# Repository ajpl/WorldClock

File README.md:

# WorldClock

This is a WorldClock implementation using Atmega 328 and DS1307 as a RTC.

## Inspiration

This project was inspired by [this](https://www.instructables.com/id/The-Wordclock-Grew-Up/) instructable that relies on a DS1302 instead of a DS1307. A couple of changes had to be made since these clocks work in different ways ([DS1302 Datasheet](https://datasheets.maximintegrated.com/en/ds/DS1302.pdf) and [DS1307 Datasheet](https://datasheets.maximintegrated.com/en/ds/DS1307.pdf)).

## How To
- Get all the parts necessary according to the Bill of Materials in Part 8 of the instructable linked above (for electronics you may use the schematic if you prefer)
- Etch the PCB using your favorite method or using a service like [OSH Park](https://oshpark.com)

- Flash the program into your Atmega 328 using your programmer of choice

- Solder every component into your PCB

- Test it out

- Follow the instructions linked above in order to build the clock's enclosure

- Put everything together

- Enjoy!

## Dependencies

- [RTC Lib](https://github.com/adafruit/RTClib)

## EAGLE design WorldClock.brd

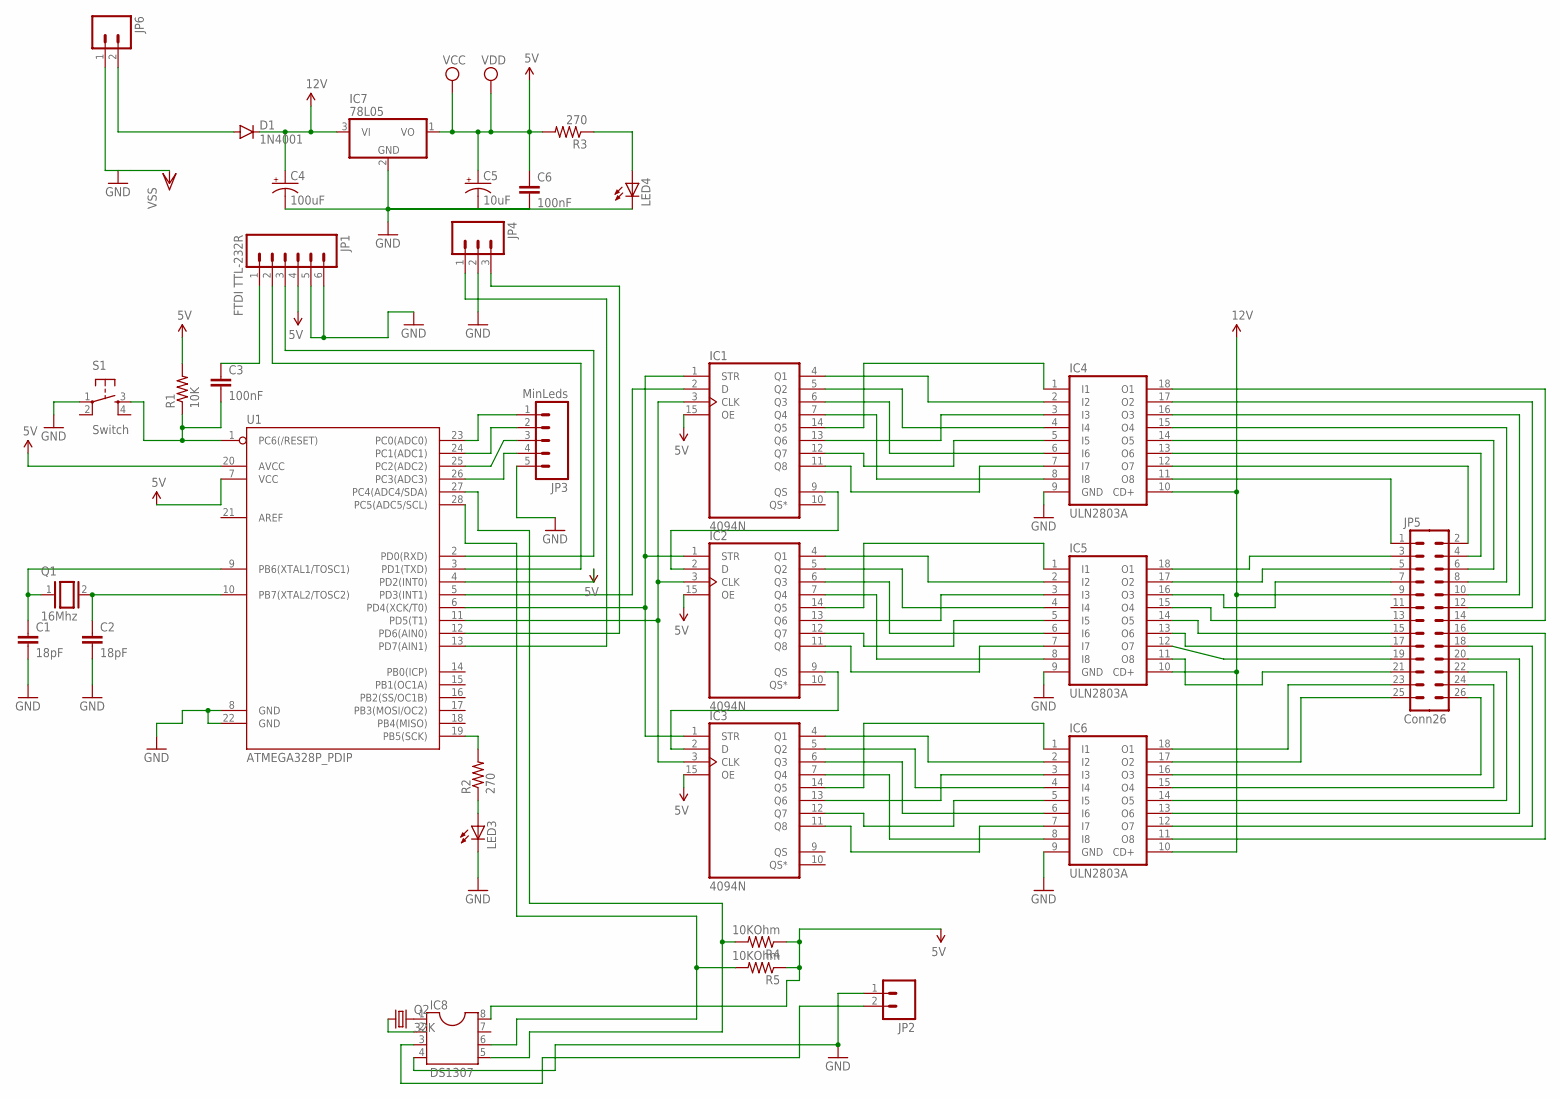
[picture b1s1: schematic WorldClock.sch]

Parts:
C1, C2: 18pF; CAP-PTH-SMALL2
C3, C6: 100nF; CAP-PTH-SMALL2
C4: 100uF; CPOL-RADIAL-100UF-25V
C5: 10uF; CPOL-RADIAL-10UF-25V
D1: 1N4001; DIODE-1N4148
IC1, IC2, IC3: 4094N; DIL16
IC4, IC5, IC6: ULN2803A; DIL18
IC7: 78L05; TO92
IC8: DS1307; SOCKET-08
JP1: FTDI TTL-232R; 1X06_NO_SILK
JP2, JP6: M025MM; SCREWTERMINAL-5MM-2
JP3: MinLeds; 1X05
JP4: M03-SCREW-5MM; SCREWTERMINAL-5MM-3
JP5: Conn26; 2X13
LED3, LED4: LED5MM
Q1: 16Mhz; QS
Q2: 32K; TC26V
R1: 10K; AXIAL-0.4
R2, R3: 270; AXIAL-0.4
R4, R5: 10KOhm; AXIAL-0.4
S1: Switch; TACTILE-PTH
U1: ATMEGA328P_PDIP; DIL28-3

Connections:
5V: C5.1 (+), C6.1, IC1.15 (OE), IC1.16 (VDD), IC2.15 (OE), IC2.16 (VDD), IC3.15 (OE), IC3.16 (VDD), IC7.1 (VO), IC8.8, JP1.4, R1.P$2 (2), R3.P$2 (2), R4.P$1 (1), R5.P$1 (1), U1.4 (PD2(INT0)), U1.7 (VCC), U1.20 (AVCC)
12V: C4.1 (+), D1.C, IC4.10 (CD+), IC5.10 (CD+), IC6.10 (CD+), IC7.3 (VI), JP5.9
GND: C1.2, C2.2, C4.2 (-), C5.2 (-), C6.2, IC1.8 (VSS), IC2.8 (VSS), IC3.8 (VSS), IC4.9 (GND), IC5.9 (GND), IC6.9 (GND), IC7.2 (GND), IC8.4, JP1.5, JP1.6, JP2.1, JP3.5, JP4.2, JP6.1, LED3.K (C), LED4.K (C), S1.1, U1.8 (GND), U1.22 (GND)
unnamed: C1.1, Q1.1, U1.9 (PB6(XTAL1/TOSC1))
unnamed: C2.1, Q1.2, U1.10 (PB7(XTAL2/TOSC2))
unnamed: C3.2, R1.P$1 (1), S1.3, U1.1 (PC6(/RESET))
unnamed: C3.1, JP1.1
unnamed: JP4.1, U1.13 (PD7(AIN1))
unnamed: JP1.2, U1.3 (PD1(TXD))
unnamed: JP1.3, U1.2 (PD0(RXD))
unnamed: JP4.3, U1.12 (PD6(AIN0))
unnamed: JP3.1, U1.23 (PC0(ADC0))
unnamed: JP3.2, U1.24 (PC1(ADC1))
unnamed: JP3.3, U1.25 (PC2(ADC2))
unnamed: JP3.4, U1.26 (PC3(ADC3))
unnamed: R2.P$2 (2), U1.19 (PB5(SCK))
unnamed: LED3.A, R2.P$1 (1)
unnamed: IC1.4 (Q1), IC4.2 (I2)
unnamed: IC1.5 (Q2), IC4.4 (I4)
unnamed: IC1.6 (Q3), IC4.6 (I6)
unnamed: IC1.7 (Q4), IC4.8 (I8)
unnamed: IC1.14 (Q5), IC4.1 (I1)
unnamed: IC1.13 (Q6), IC4.3 (I3)
unnamed: IC1.12 (Q7), IC4.5 (I5)
unnamed: IC1.11 (Q8), IC4.7 (I7)
unnamed: IC1.9 (QS), IC2.2 (D)
unnamed: IC2.4 (Q1), IC5.2 (I2)
unnamed: IC2.5 (Q2), IC5.4 (I4)
unnamed: IC2.6 (Q3), IC5.6 (I6)
unnamed: IC2.7 (Q4), IC5.8 (I8)
unnamed: IC2.14 (Q5), IC5.1 (I1)
unnamed: IC2.13 (Q6), IC5.3 (I3)
unnamed: IC2.12 (Q7), IC5.5 (I5)
unnamed: IC2.11 (Q8), IC5.7 (I7)
unnamed: IC2.9 (QS), IC3.2 (D)
unnamed: IC3.4 (Q1), IC6.2 (I2)
unnamed: IC3.5 (Q2), IC6.4 (I4)
unnamed: IC3.6 (Q3), IC6.6 (I6)
unnamed: IC3.7 (Q4), IC6.8 (I8)
unnamed: IC3.14 (Q5), IC6.1 (I1)
unnamed: IC3.13 (Q6), IC6.3 (I3)
unnamed: IC3.12 (Q7), IC6.5 (I5)
unnamed: IC3.11 (Q8), IC6.7 (I7)
unnamed: IC1.2 (D), U1.5 (PD3(INT1))
unnamed: IC1.1 (STR), IC2.1 (STR), IC3.1 (STR), U1.6 (PD4(XCK/T0))
unnamed: IC1.3 (CLK), IC2.3 (CLK), IC3.3 (CLK), U1.11 (PD5(T1))
unnamed: IC5.14 (O5), JP5.15
unnamed: LED4.A, R3.P$1 (1)
unnamed: IC5.13 (O6), JP5.17
unnamed: IC4.11 (O8), JP5.1
unnamed: D1.A, JP6.2
unnamed: IC4.12 (O7), JP5.2
unnamed: IC4.13 (O6), JP5.4
unnamed: IC4.14 (O5), JP5.6
unnamed: IC4.15 (O4), JP5.8
unnamed: IC4.16 (O3), JP5.10
unnamed: IC4.17 (O2), JP5.12
unnamed: IC4.18 (O1), JP5.14
unnamed: IC5.18 (O1), JP5.3
unnamed: IC5.17 (O2), JP5.5
unnamed: IC5.16 (O3), JP5.7
unnamed: IC5.15 (O4), JP5.13
unnamed: IC5.12 (O7), JP5.19
unnamed: IC6.18 (O1), JP5.23
unnamed: IC5.11 (O8), JP5.21
unnamed: IC6.17 (O2), JP5.25
unnamed: IC6.16 (O3), JP5.26
unnamed: IC6.15 (O4), JP5.24
unnamed: IC6.14 (O5), JP5.22
unnamed: IC6.13 (O6), JP5.20
unnamed: IC6.12 (O7), JP5.18
unnamed: IC6.11 (O8), JP5.16
unnamed: IC8.6, R5.P$2 (2), U1.28 (PC5(ADC5/SCL))
unnamed: IC8.3, JP2.2
unnamed: IC8.5, R4.P$2 (2), U1.27 (PC4(ADC4/SDA))
unnamed: IC8.1, Q2.2
unnamed: IC8.2, Q2.1

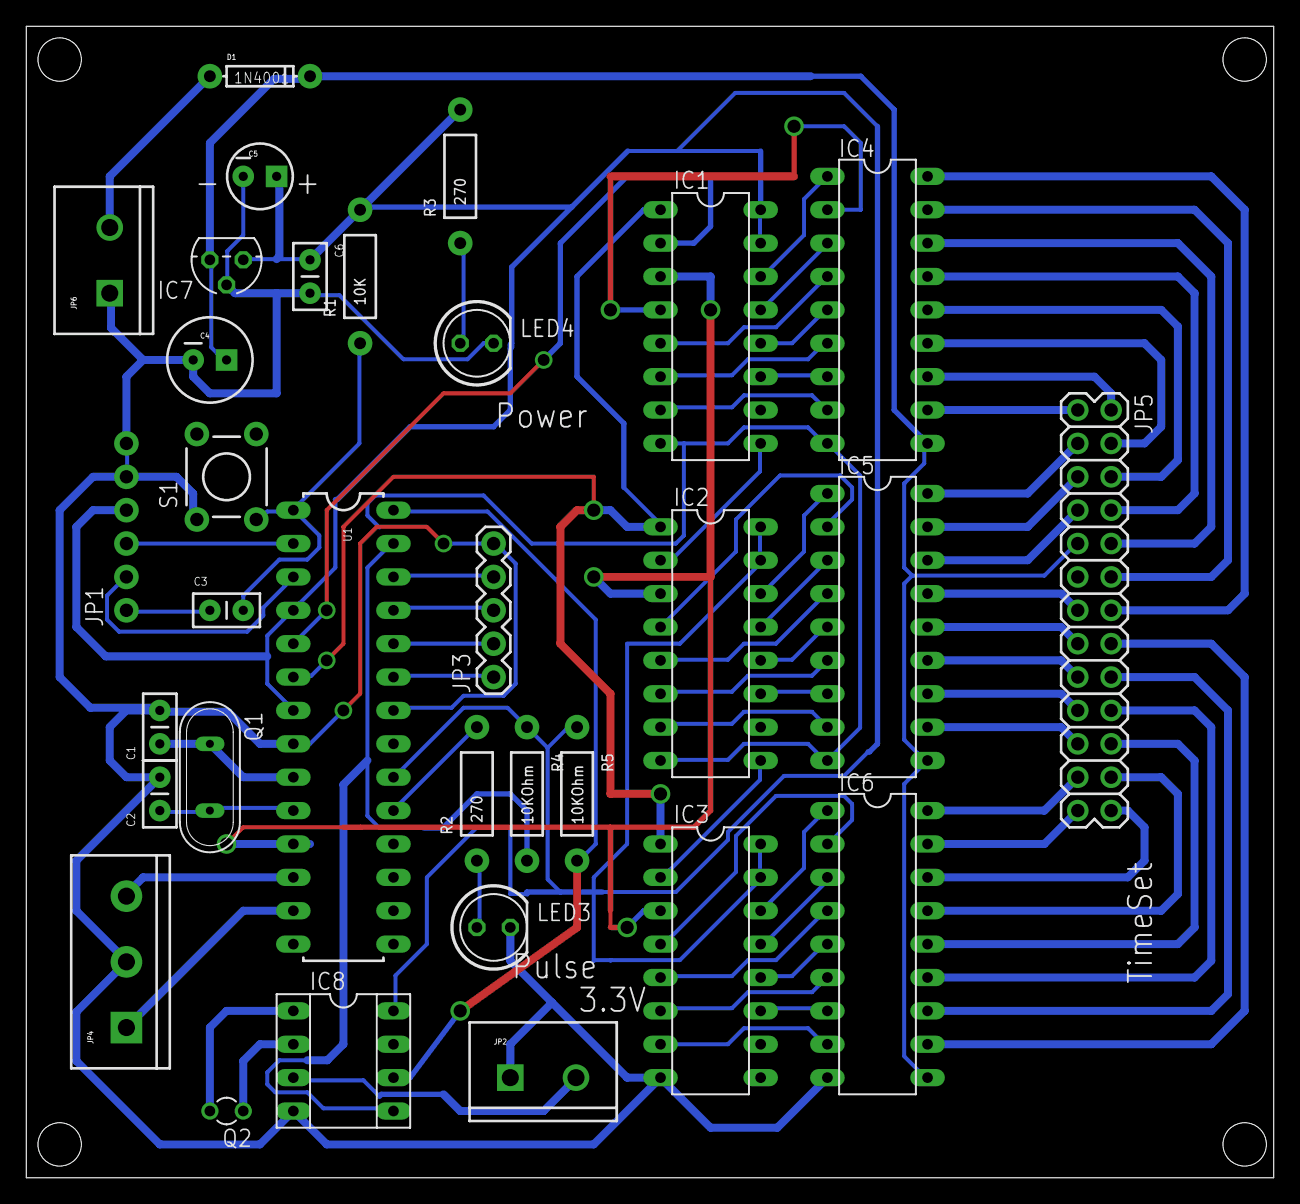
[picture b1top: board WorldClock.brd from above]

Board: 2 copper layers, 94.9 x 87.6 mm, 36 parts (0 on the bottom side), 77 nets.

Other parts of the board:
U$1, U$2, U$3, U$4: STAND-OFF

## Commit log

2019-03-13 Arduino program
2019-03-13 PCB design and schematics

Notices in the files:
parts and their libraries:
SparkFun-Passives: Licensing: Creative Commons ShareAlike 4.0 International - https://creativecommons.org/licenses/by-sa/4.0
